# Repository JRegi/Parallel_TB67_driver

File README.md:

# Parallel_TB67_driver
little repositorie for little pcb

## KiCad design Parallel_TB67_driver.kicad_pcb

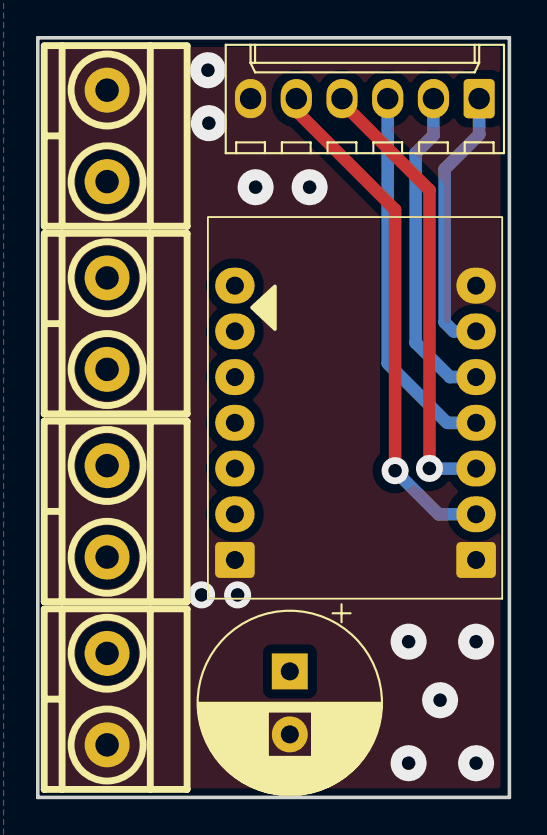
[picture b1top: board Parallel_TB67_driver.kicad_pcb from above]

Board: 2 copper layers, 26.2 x 42.2 mm, 7 parts (0 on the bottom side), 11 nets.

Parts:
C1: 220uF; CP_Radial_D10.0mm_P3.50mm
J1: Vin; BORNERA2_AZUL
J2: Vout; BORNERA2_AZUL
J3: Driver_pinout; Molex_KK-254_AE-6410-06A_1x06_P2.54mm_Vertical
J4: MotorA; BORNERA2_AZUL
J5: MotorB; BORNERA2_AZUL
U1: Driver Module; Dual-Driver-Module

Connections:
/IN_A1: J3.1, U1.6 (IN_A1)
/IN_A2: J3.2, U1.5 (IN_A2)
/IN_B1: J3.4, U1.3 (IN_B1)
/IN_B2: J3.5, U1.2 (IN_B2)
/OUT_A1: J4.1, U1.11 (OUT_A1)
/OUT_A2: J4.2, U1.10 (OUT_A2)
/OUT_B1: J5.1, U1.8 (OUT_B1)
/OUT_B2: J5.2, U1.7 (OUT_B2)
/VM: C1.1, J1.1 (Pin_2), J2.2, U1.9 (VM)
/VREF: J3.3, U1.4 (VREF)
GND: C1.2, J1.2 (Pin_1), J2.1, J3.6, U1.1 (GND)

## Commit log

2024-10-04 Schematic & footprint assignment
2024-10-04 Capacitors sch & components placement
2024-10-07 PCB completed
2024-10-10 back-up
2024-10-10 Fixed bottom layer molex pins connection
